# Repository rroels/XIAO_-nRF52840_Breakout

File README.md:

# Seeed XIAO nRF52840 breakout board

> [!WARNING]
> The information and material (code, designs, files, ...) are provided "AS IS". We make no representation or warranty of any kind, express or implied, regarding the accuracy, adequacy, validity, reliability, availability, or completeness of any information or material. Use this at your own risk.

> [!WARNING]
> Note that some batteries have a "reversed" plug with the positive and negatives wires switched, so always make sure that the polarity matches the indications on the board, before plugging anything in!

## Introduction

This repository contains a small breakout board for the Seeed XIAO nRF52840.

Note that there exists an official XIAO expansion board:
[https://wiki.seeedstudio.com/Seeeduino-XIAO-Expansion-Board/](https://wiki.seeedstudio.com/Seeeduino-XIAO-Expansion-Board/)

However, for my projects this was not sufficient because:

* it does not break out all pins on the underside of the XIAO 
* the expansion board takes away some of the already limited pins for the OLED, buzzer, buttons, ...
* some pins are exposed in their grove connector format, which is not always desired

For this reason I designed my own breakout board, with all pins being exposed (including the pads on the bottom of the XIAO). Most importantly, this provides easy access to the SWD pins on the underside, for easy flashing and debugging. 

## Change Log
* v1.1
  * Added extra pins for BAT- and BAT+
* v1.0
  * Initial design 
 
## Design Considerations

The goals are the following:

* break out all pad on the underside:
* 
* pads on the underside should connect to the breakout board via pogo pins, to avoid having to solder things to the underside of the XIAO.
* battery connector 
* maintain compatibility with breadboards
* a big reset button, as the on-board button is difficult to reach
* keep the width of the board close to the XIAO width

## How to Obtain the Physical PCB

The Gerber file is in this repository (`gerber/xiao_nrf52840_breakout.zip`). Simply upload this file a PCB manufacturer of your choice (JLPCB, PCBWay, ...), and you they will make it for you for as low as \$5 for 5 pieces (with the cheapest shipping option, which can take a few weeks).

For JLCPCB, select the order number option where they will replace "JLCJLCJLCJLC" on the board with the actual order number.

> [!WARNING]
> Note that you will still have to solder the components onto the PCB yourself!

## Bill of Materials (BOM)

* 1 x Molex 53261-0271 battery connector (or similar)
* 1 x "2x2" DIP Pogo Pins, 12mm
* 4 x DIP Pogo Pin, 12mm

## How to Edit Design

Everything you need to edit this design in KiCad 8 is included in the repository.

However, this project uses symbols, footprints and 3D models from [Component Search Engine](https://componentsearchengine.com/). Their license allows us to do pretty much whatever we want with them, except redistributing them. For this reason I can't include them in this repository.

If you would like to edit the design yourself, you will need to download the following component libraries from [https://componentsearchengine.com/](https://componentsearchengine.com/) (it's free!):

* [https://componentsearchengine.com/part-view/53261-0271/Molex](https://componentsearchengine.com/part-view/53261-0271/Molex)
* [https://componentsearchengine.com/part-view/MJTP1243/Apem](https://componentsearchengine.com/part-view/MJTP1243/Apem)

You also need these 3D models for the preview:
* [https://grabcad.com/library/seeed-studio-xiao-nrf52840-sense-1](https://grabcad.com/library/seeed-studio-xiao-nrf52840-sense-1)
* [https://www.printables.com/model/563073-seeed-studio-xiao-nrf52840/files](https://www.printables.com/model/563073-seeed-studio-xiao-nrf52840/files) 

From the downloaded zip files, move the content of the `KiCad` and `3D` subfolders into the project structure, so that the end-result looks like this:

The KiCad project is configured to look for these files in these locations, using relative paths, so no changes to the project itself are required.

## Related Sources

* [https://www.seeedstudio.com/Seeed-XIAO-BLE-nRF52840-p-5201.html](https://www.seeedstudio.com/Seeed-XIAO-BLE-nRF52840-p-5201.html)
* [https://www.seeedstudio.com/Seeed-XIAO-BLE-Sense-nRF52840-p-5253.html](https://www.seeedstudio.com/Seeed-XIAO-BLE-Sense-nRF52840-p-5253.html)
* [https://wiki.seeedstudio.com/XIAO_BLE/](https://wiki.seeedstudio.com/XIAO_BLE/)
* [https://www.printables.com/model/563073-seeed-studio-xiao-nrf52840/files](https://www.printables.com/model/563073-seeed-studio-xiao-nrf52840/files)
* [https://grabcad.com/library/seeed-studio-xiao-nrf52840-sense-1](https://grabcad.com/library/seeed-studio-xiao-nrf52840-sense-1)

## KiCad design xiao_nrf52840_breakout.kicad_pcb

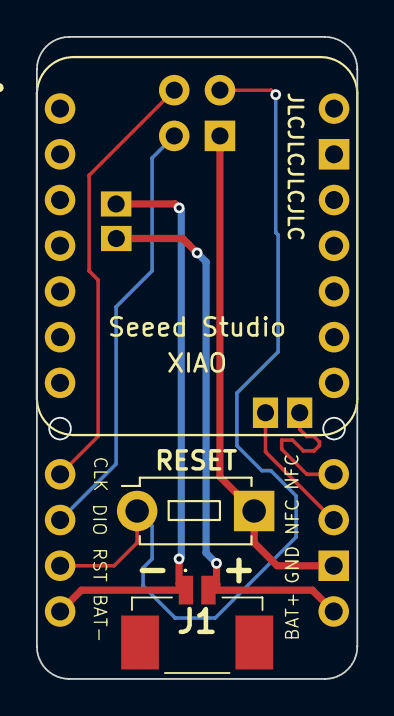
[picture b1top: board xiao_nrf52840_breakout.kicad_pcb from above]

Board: 2 copper layers, 17.8 x 35.7 mm, 12 parts (0 on the bottom side), 8 nets.

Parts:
J1: 53261-0271; 532610271
J2, J3: Conn_01x07; PinSocket_1x07_P2.54mm_Vertical
J4, J8, J9, J10: Conn_01x01; PinHeader_1x01_P2.54mm_Vertical
J5, J7: Conn_01x04; PinSocket_1x04_P2.54mm_Vertical
J6: Conn_02x02_Odd_Even; PinHeader_2x02_P2.54mm_Vertical
SW1: SW_Push; SW_PUSH_1P1T_6x3.5mm_H4.3_APEM_MJTP1243
U1: Seeed Studio XIAO nRF52840; XIAO-nRF52840-Sense-14P-2.54-21X17.8MM

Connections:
BAT+: J1.2, J5.4, J10.1
BAT-: J1.1, J7.4, J9.1
GND: J5.3, J6.4, SW1.2
unnamed: J4.1, J5.1
unnamed: J5.2, J8.1
RESET: J6.2, J7.3, SW1.1
SWCLK: J6.1, J7.1
SWDIO: J6.3, J7.2

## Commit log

2024-08-04 add gitignore
2024-08-04 update gitignore
2024-08-04 add gerber files
2024-08-04 add kicad files
2024-08-04 add readme
2024-08-04 add lib dir
2024-08-04 update images
2024-08-13 add extra bat+ and bat- pins
